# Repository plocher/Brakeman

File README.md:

# Brakeman
## License: CERN Open Hardware Licence v1.2

An electronic DCC-track-driven figurine with a red or blue LED

## GCOR Rule 6.19 D (paraphrased)
> When a train stops on a main track, flag protection must be provided
> On a layout, torpedoes and fusees are a bit over the top, but a
> brakeman/flagman with a red lantern can add a twist to your next operating
> session.  Adopt prototype practices and have your crews protect
> their trains when switching a town or otherwise fouling the main.
> Just don't forget to recall the flagman before leaving town!

## Designed in the NMRA/PCR for DCC layouts

Assembly required
 
1. V1.0-1.3: Use a track nipper to detach the base from the hand holding the LED.
1. V1.4: Snap the base from the feet and remove any extra PCB frame from around the figure.
1. Solder the two feet to the two small gold pads on the top of the base
1. You can solder a wire (the clipped off resistor leads work well) to strengthen and align this connection
1. Attach the weight to the top of the base next to (but not touching) his feet with double sided foam tape
1. Place the large gold pads across the rails to light the red lantern.

Variation:
  * Make a "Safety Sam" to indicate track or rolling stock that must not be used/moved.  Use 2 BLUE LEDs instead of one RED one - solder them "back to back, opposite" so that one LED's long lead is soldered to the "front" on the raised hand, while the other's long lead is soldered to the figure's "back" on the lowered hand.  Using 2x Blue LEDS is necessary because the Blue LED's have a reverse breakdown voltage close to 5v, while the common Red ones seem to be able to handle 20v+.  (DCC track voltage is ~15v...)

Clean track works best.  Use violates UP Safety Rule 81.2.1, Step Over Rail 

John Plocher, SPCoast.com

> WARNING: This product may contain chemicals known to the State of California to cause cancer and birth defects or other reproductive harm. 

  * Designed for fabrication and ease of assembly

For best results when fab'ing, choose:

  * ENIG (gold) rather than a Hot Air Solder Layer (HASL) for the pads
  * White or Blue soldermask
  * Panalize = 1

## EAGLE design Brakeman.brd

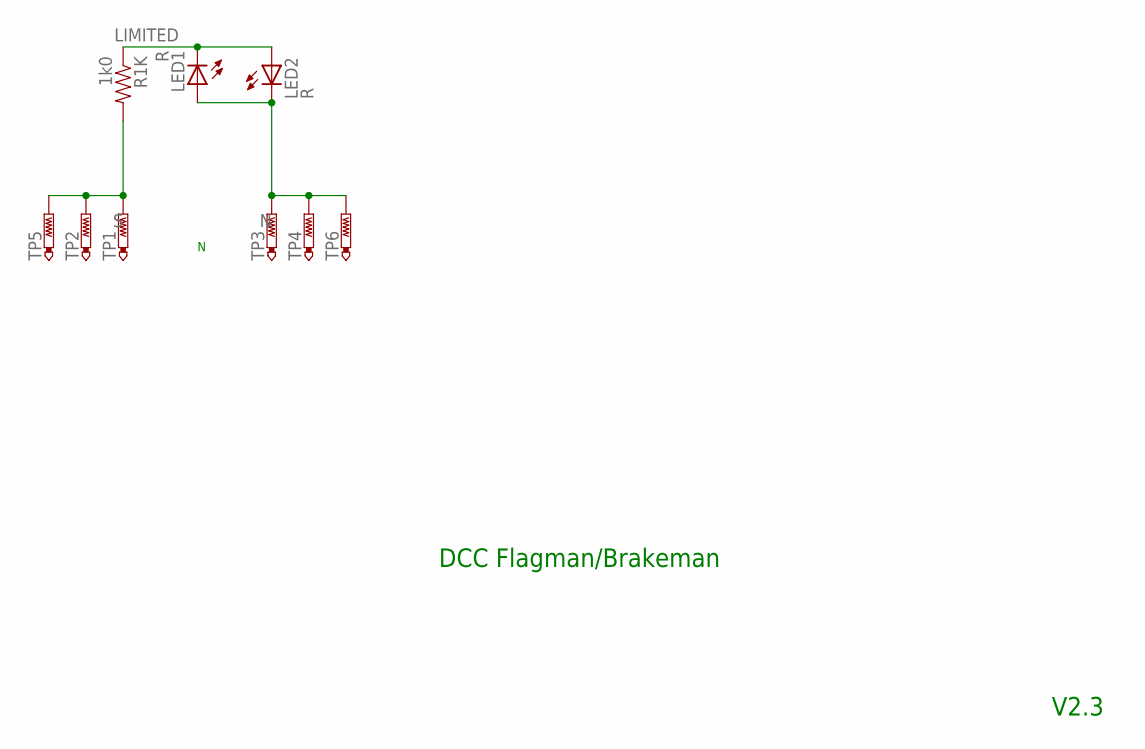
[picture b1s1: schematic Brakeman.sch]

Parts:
LED1, LED2: R; 0603-LED
R1K: 1k0; 0603-RES
TP1, TP2, TP3, TP4, TP5, TP6: PTR1PAD1-13; P1-13

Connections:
LIMITED: LED1.C, LED2.A, R1K.1
N: LED1.A, LED2.C, TP3.TP, TP4.TP, TP6.TP
S: R1K.2, TP1.TP, TP2.TP, TP5.TP

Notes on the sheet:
DCC Flagman/Brakeman
V2.3

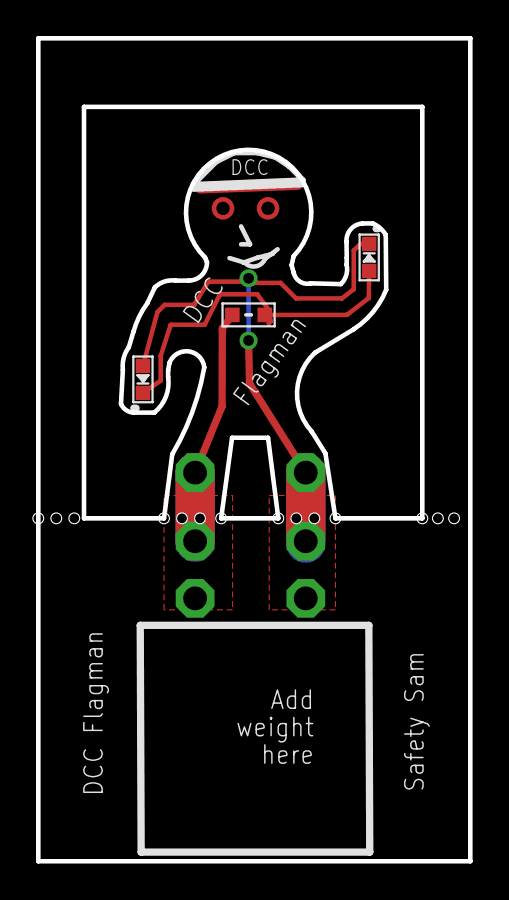
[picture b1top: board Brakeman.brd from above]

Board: 2 copper layers, 24.0 x 45.7 mm, 9 parts (0 on the bottom side), 3 nets.

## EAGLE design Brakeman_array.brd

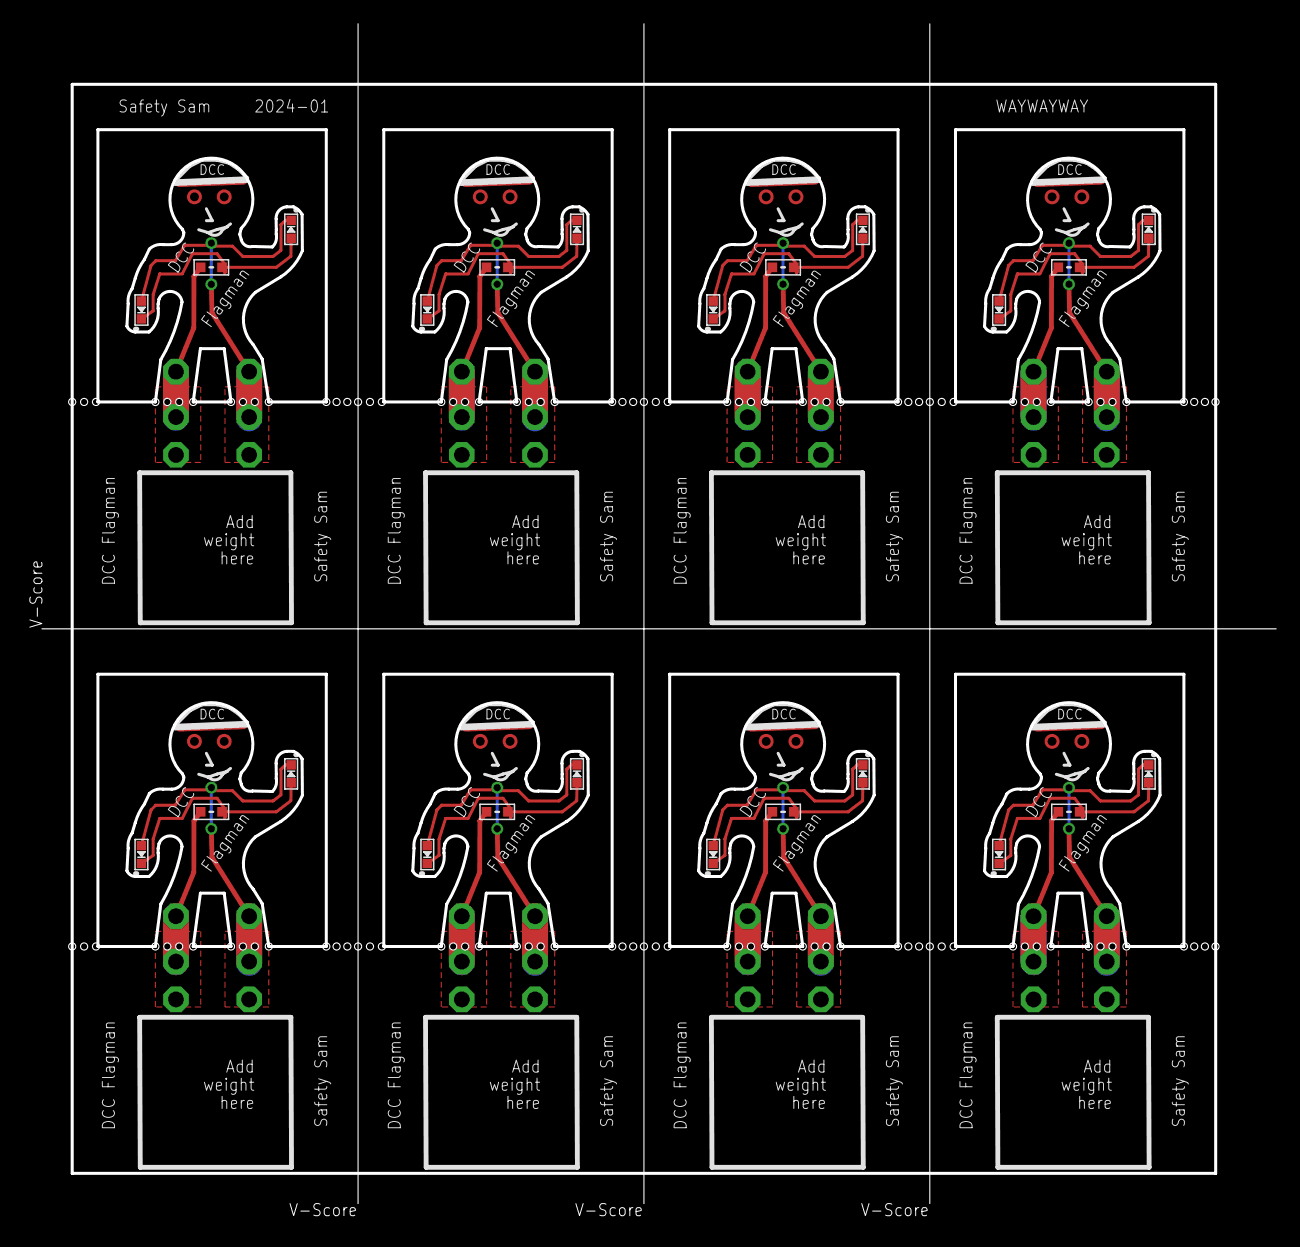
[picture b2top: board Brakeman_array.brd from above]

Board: 2 copper layers, 104.9 x 100.4 mm, 72 parts (0 on the bottom side), 24 nets.

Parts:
LED1X11, LED1X12, LED1X21, LED1X22, LED1X31, LED1X32, LED1X41, LED1X42, LED2X11, LED2X12, LED2X21, LED2X22, LED2X31, LED2X32, LED2X41, LED2X42: R; 0603-LED
R1KX11, R1KX12, R1KX21, R1KX22, R1KX31, R1KX32, R1KX41, R1KX42: 1k0; 0603-RES
TP1X11, TP1X12, TP1X21, TP1X22, TP1X31, TP1X32, TP1X41, TP1X42, TP2X11, TP2X12, TP2X21, TP2X22, TP2X31, TP2X32, TP2X41, TP2X42, TP3X11, TP3X12, TP3X21, TP3X22, TP3X31, TP3X32, TP3X41, TP3X42, TP4X11, TP4X12, TP4X21, TP4X22, TP4X31, TP4X32, TP4X41, TP4X42, TP5X11, TP5X12, TP5X21, TP5X22, TP5X31, TP5X32, TP5X41, TP5X42, TP6X11, TP6X12, TP6X21, TP6X22, TP6X31, TP6X32, TP6X41, TP6X42: PTR1PAD1-13; P1-13

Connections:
LIMITEDX11: LED1X11.C, LED2X11.A, R1KX11.1
LIMITEDX12: LED1X12.C, LED2X12.A, R1KX12.1
LIMITEDX21: LED1X21.C, LED2X21.A, R1KX21.1
LIMITEDX22: LED1X22.C, LED2X22.A, R1KX22.1
LIMITEDX31: LED1X31.C, LED2X31.A, R1KX31.1
LIMITEDX32: LED1X32.C, LED2X32.A, R1KX32.1
LIMITEDX41: LED1X41.C, LED2X41.A, R1KX41.1
LIMITEDX42: LED1X42.C, LED2X42.A, R1KX42.1
NX11: LED1X11.A, LED2X11.C, TP3X11.TP, TP4X11.TP, TP6X11.TP
NX12: LED1X12.A, LED2X12.C, TP3X12.TP, TP4X12.TP, TP6X12.TP
NX21: LED1X21.A, LED2X21.C, TP3X21.TP, TP4X21.TP, TP6X21.TP
NX22: LED1X22.A, LED2X22.C, TP3X22.TP, TP4X22.TP, TP6X22.TP
NX31: LED1X31.A, LED2X31.C, TP3X31.TP, TP4X31.TP, TP6X31.TP
NX32: LED1X32.A, LED2X32.C, TP3X32.TP, TP4X32.TP, TP6X32.TP
NX41: LED1X41.A, LED2X41.C, TP3X41.TP, TP4X41.TP, TP6X41.TP
NX42: LED1X42.A, LED2X42.C, TP3X42.TP, TP4X42.TP, TP6X42.TP
SX11: R1KX11.2, TP1X11.TP, TP2X11.TP, TP5X11.TP
SX12: R1KX12.2, TP1X12.TP, TP2X12.TP, TP5X12.TP
SX21: R1KX21.2, TP1X21.TP, TP2X21.TP, TP5X21.TP
SX22: R1KX22.2, TP1X22.TP, TP2X22.TP, TP5X22.TP
SX31: R1KX31.2, TP1X31.TP, TP2X31.TP, TP5X31.TP
SX32: R1KX32.2, TP1X32.TP, TP2X32.TP, TP5X32.TP
SX41: R1KX41.2, TP1X41.TP, TP2X41.TP, TP5X41.TP
SX42: R1KX42.2, TP1X42.TP, TP2X42.TP, TP5X42.TP

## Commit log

2019-12-09 added graphic
2020-05-04 updated tags
2020-10-05 added values for connectors
2024-01-12 Version 2.4
2024-01-12 Revert "Version 2.4"
    This reverts commit de817f9b6bc09cb4258c25781ce6263bd1cc7bce.
2024-01-12 smt and 2x LEDs
2024-01-13 Version 2.5
2024-01-13 updated metadata
2024-01-13 added foot tiedowns
2024-01-17 fixed silkscreen/layer issues with PCBWay
